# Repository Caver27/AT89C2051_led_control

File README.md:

# Układ sterujący 8 diodami led przy pomocy 4 przycisków w oparciu o mikrokontroler AT89C2051

## Schemat ideowy układu

## Schemat połączeń płytki

## Wykorzystane narzędzia
* Autodesk Eagle 9.6.2

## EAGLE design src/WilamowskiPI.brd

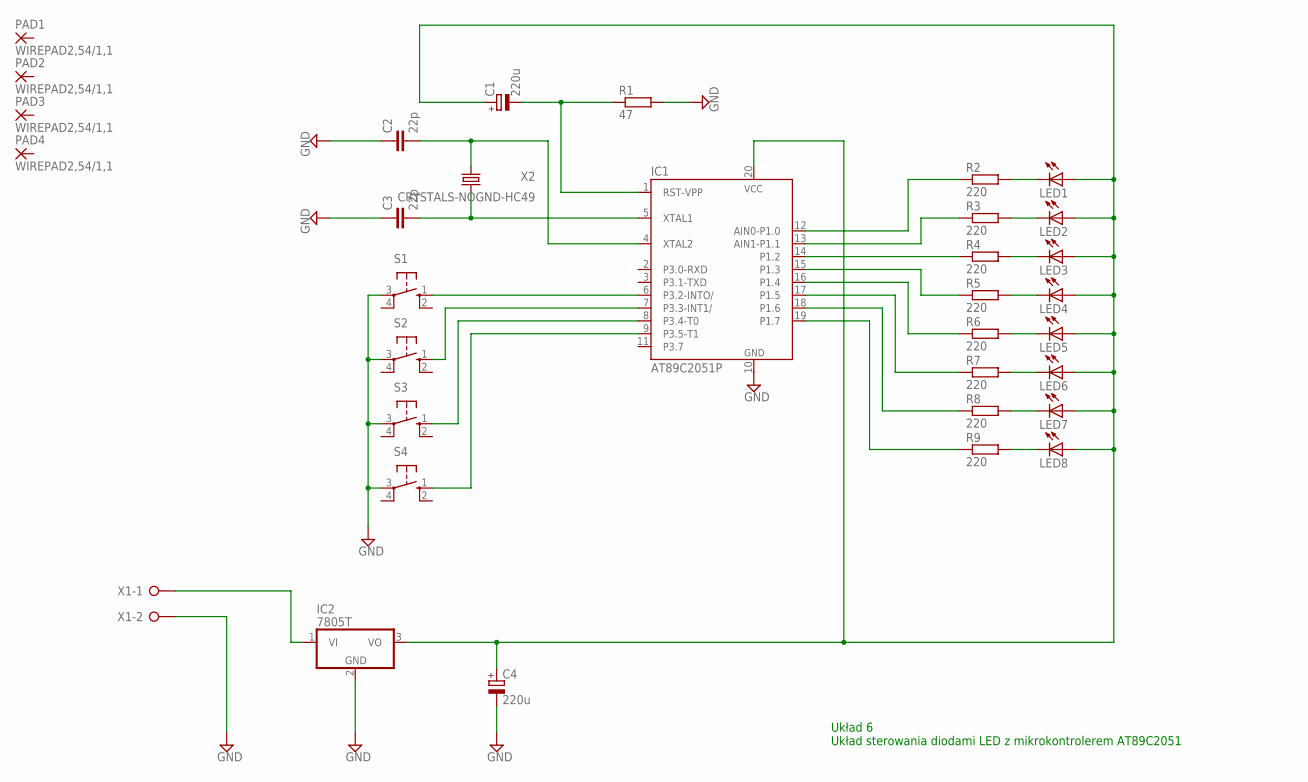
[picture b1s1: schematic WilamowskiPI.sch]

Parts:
C1, C4: 220u; E3,5-8
C2, C3: 22p; C1206
IC1: AT89C2051P; DIL20
IC2: 7805T; TO220H
LED1, LED2, LED3, LED4, LED5, LED6, LED7, LED8: LED3MM
PAD1, PAD2, PAD3, PAD4: WIREPAD2,54/1,1; 2,54/1,1
R1: 47; R1206
R2, R3, R4, R5, R6, R7, R8, R9: 220; R1206
S1, S2, S3, S4: 10-XX; B3F-10XX
X1: W237-02P; W237-132
X2: CRYSTALS-NOGND-HC49; HC49

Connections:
GND: C2.1, C3.1, C4.-, IC1.10 (GND), IC2.2 (GND), R1.2, S1.3, S2.3, S3.3, S4.3, X1.2
unnamed: C1.-, IC1.1 (RST-VPP), R1.1
unnamed: C2.2, IC1.4 (XTAL2), X2.2
unnamed: C3.2, IC1.5 (XTAL1), X2.1
unnamed: IC1.9 (P3.5-T1), S4.1 (S)
unnamed: IC1.6 (P3.2-INTO/), S1.1 (S)
unnamed: IC1.7 (P3.3-INT1/), S2.1 (S)
unnamed: IC1.8 (P3.4-T0), S3.1 (S)
unnamed: IC1.12 (AIN0-P1.0), R2.1
unnamed: IC1.13 (AIN1-P1.1), R3.1
unnamed: IC1.14 (P1.2), R4.1
unnamed: IC1.15 (P1.3), R5.1
unnamed: IC1.16 (P1.4), R6.1
unnamed: IC1.17 (P1.5), R7.1
unnamed: IC1.18 (P1.6), R8.1
unnamed: IC1.19 (P1.7), R9.1
unnamed: C1.+, C4.+, IC1.20 (VCC), IC2.3 (VO), LED1.A, LED2.A, LED3.A, LED4.A, LED5.A, LED6.A, LED7.A, LED8.A
unnamed: LED1.K (C), R2.2
unnamed: LED2.K (C), R3.2
unnamed: LED3.K (C), R4.2
unnamed: LED4.K (C), R5.2
unnamed: LED5.K (C), R6.2
unnamed: LED6.K (C), R7.2
unnamed: LED7.K (C), R8.2
unnamed: LED8.K (C), R9.2
unnamed: IC2.1 (VI), X1.1

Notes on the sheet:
Układ 6 Układ sterowania diodami LED z mikrokontrolerem AT89C2051

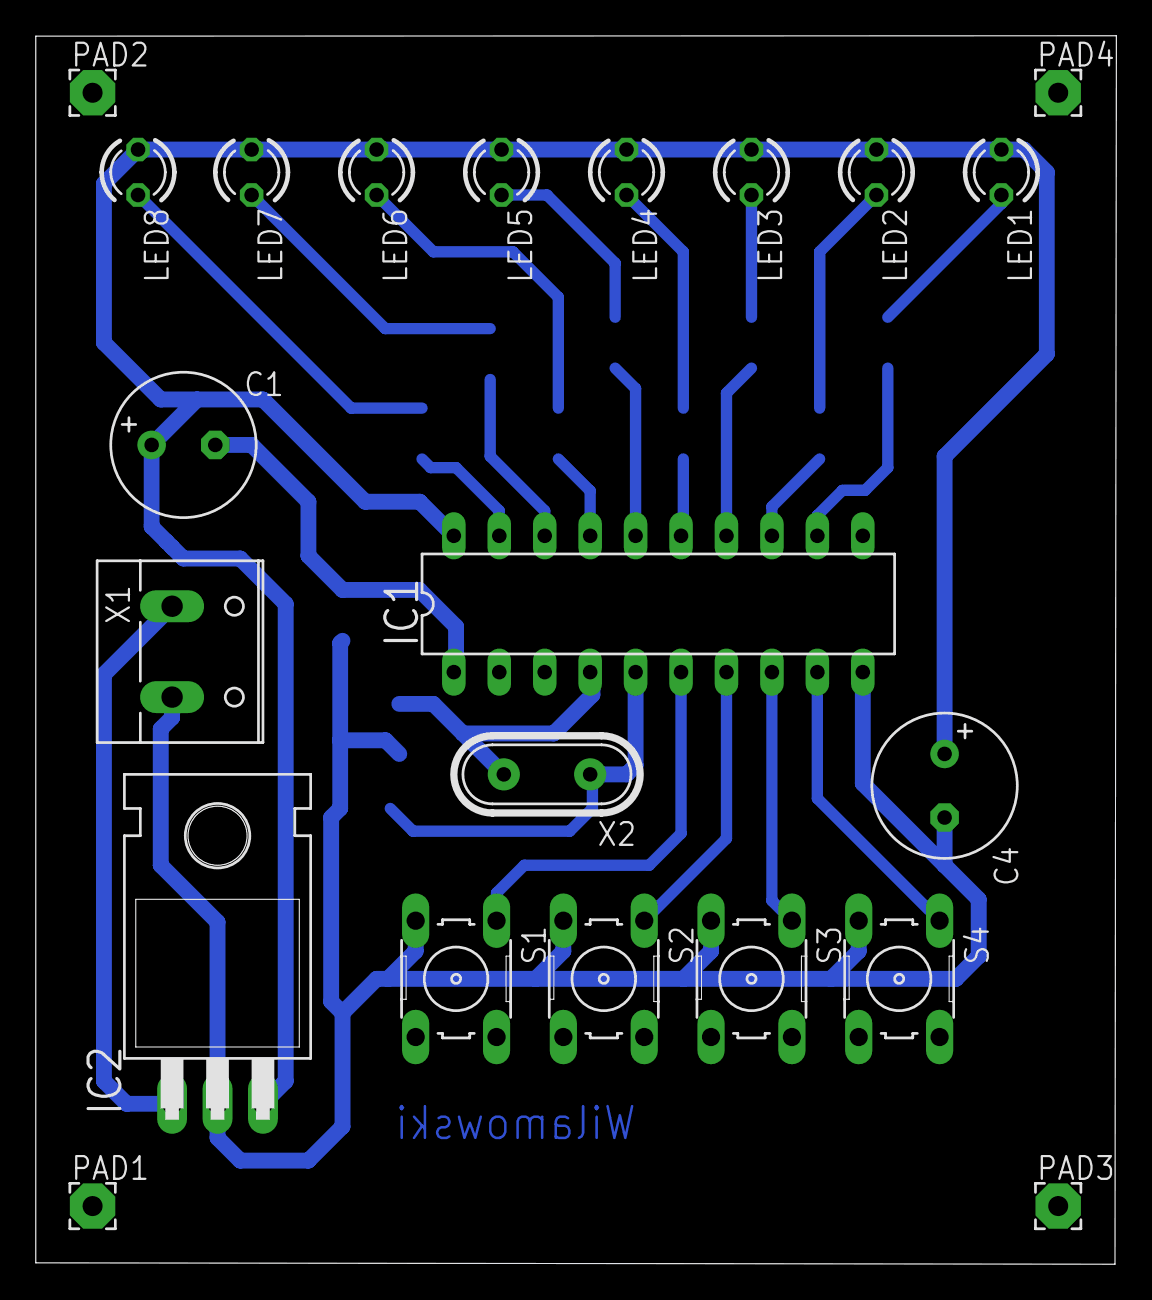
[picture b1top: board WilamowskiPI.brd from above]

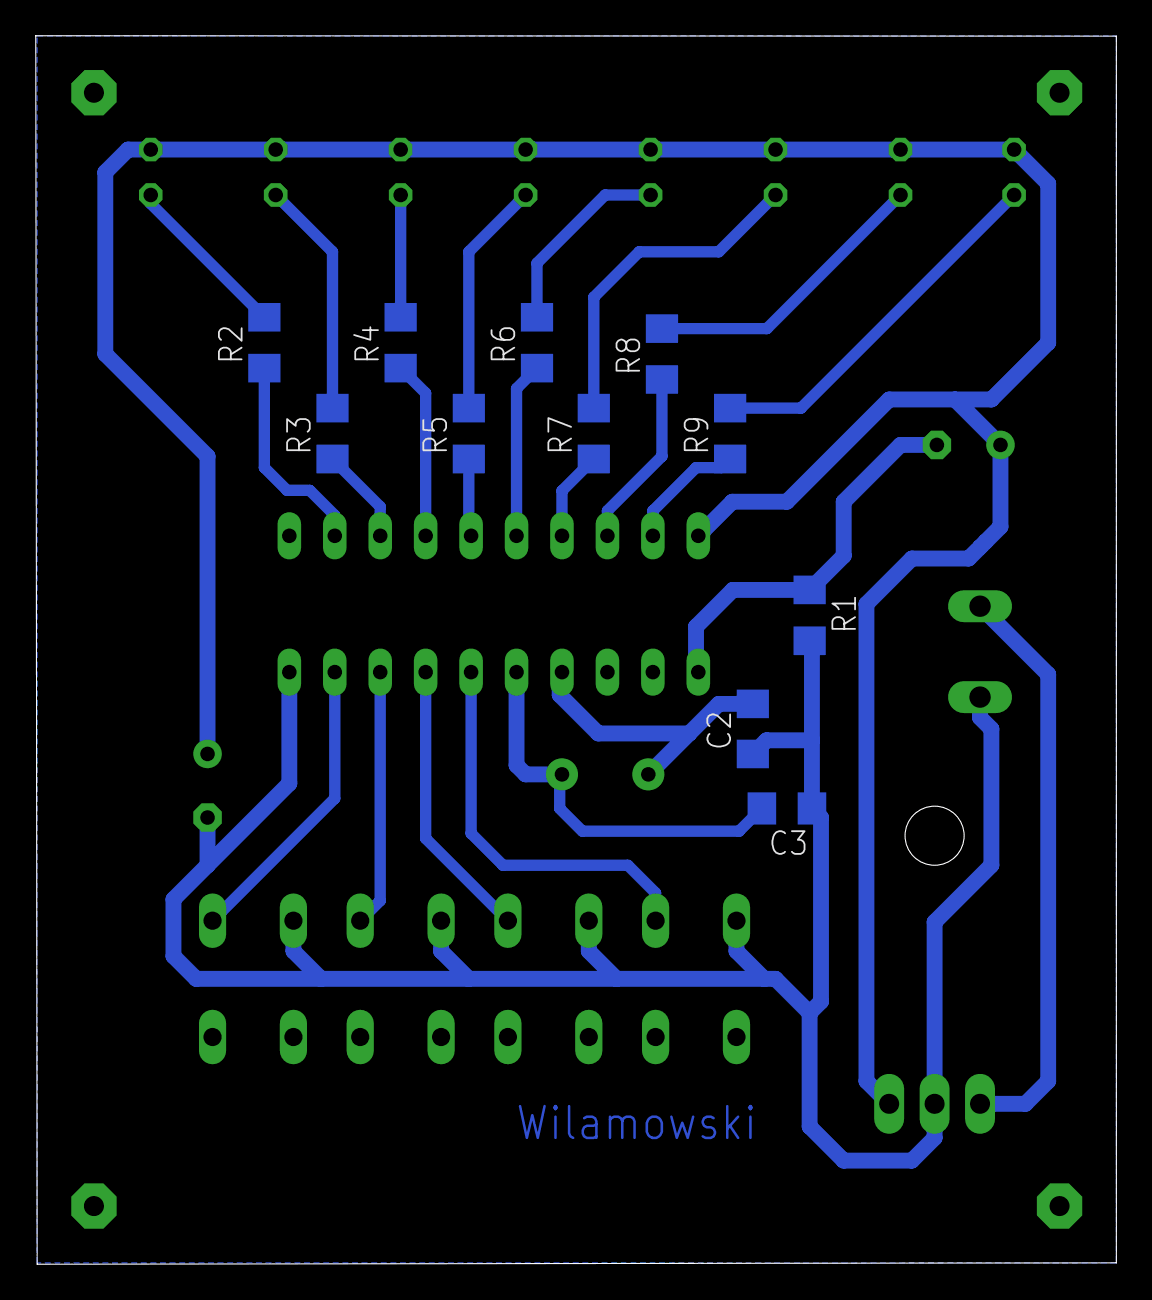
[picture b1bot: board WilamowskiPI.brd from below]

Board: 2 copper layers, 60.4 x 68.7 mm, 33 parts (11 on the bottom side), 26 nets.
